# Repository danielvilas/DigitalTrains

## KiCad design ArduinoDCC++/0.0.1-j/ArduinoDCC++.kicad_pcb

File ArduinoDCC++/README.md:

# Arduino DCC++ Board
This board is designed to have the arduino core and the motor shield on one single board. 
One objective is to study the pinout change of the motor shield for DCC++

## Status
Deprecated, The new Dcc++EX project have an updated pinout that solves the need of this board. Also, for the shake of the price, this board has been separated on several independent boards, under [DccBlock](../DccBlocks) project.

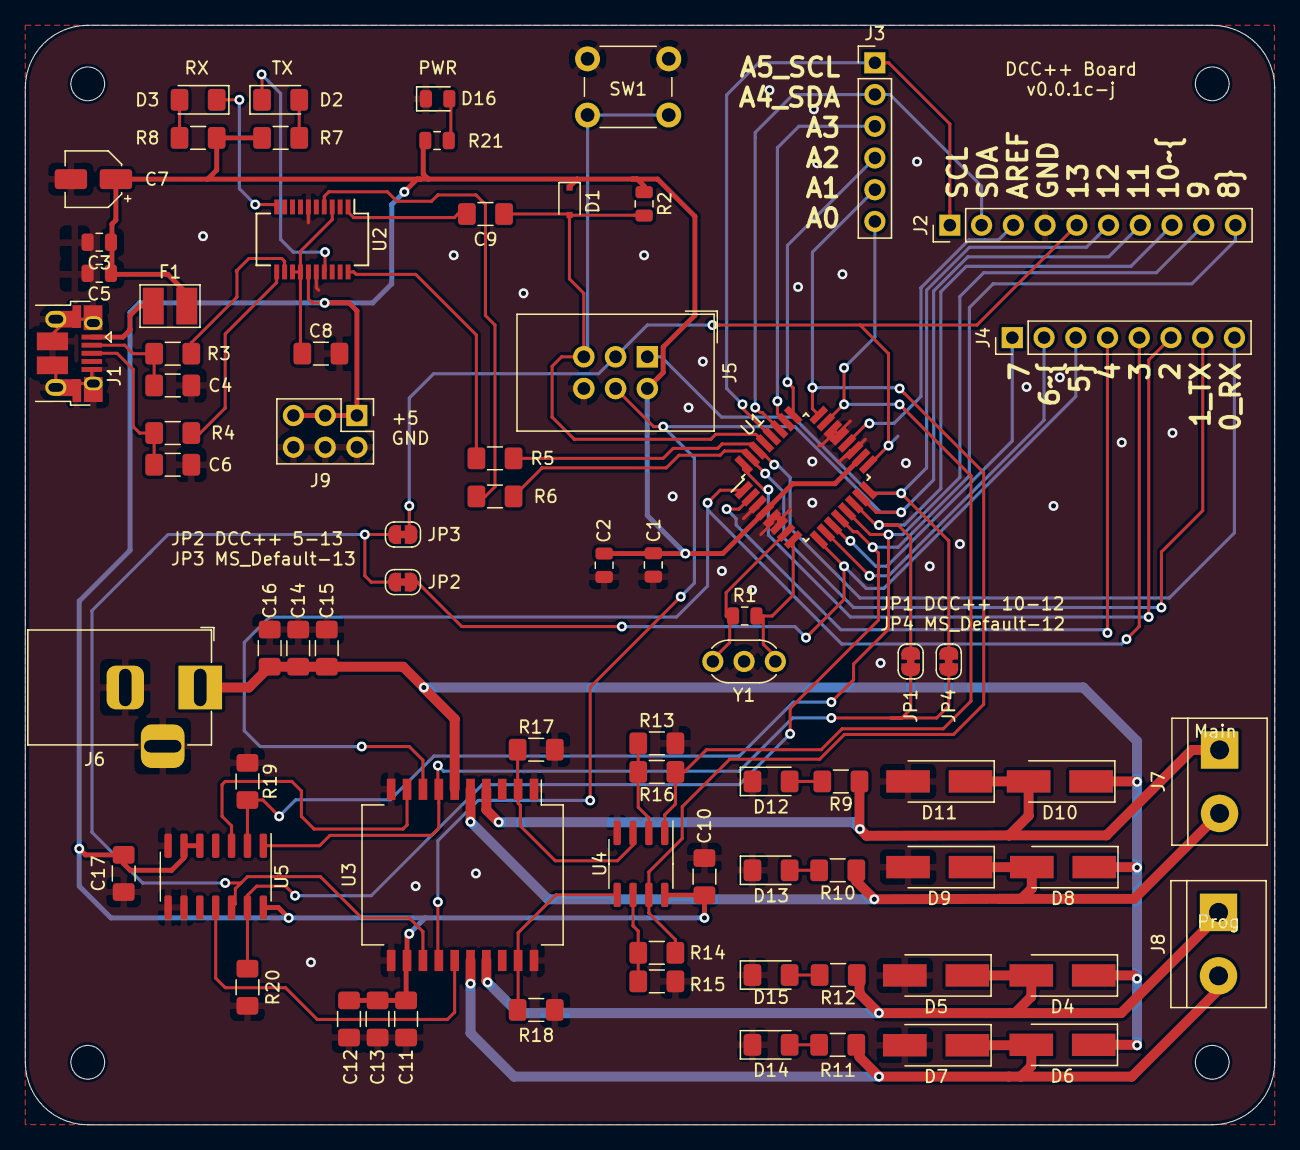
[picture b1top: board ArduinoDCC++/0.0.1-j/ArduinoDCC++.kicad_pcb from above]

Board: 2 copper layers, 100.0 x 88.0 mm, 79 parts (0 on the bottom side), 57 nets.

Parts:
C1, C2, C5: 100nF; C_0805_2012Metric
C3: 10nF; C_0805_2012Metric
C4, C6: 47pF; C_1206_3216Metric_Pad1.42x1.75mm_HandSolder
C7: 4.7uf; CP_Elec_4x5.3
C8, C9, C10, C11, C13, C17: 100nF; C_1206_3216Metric_Pad1.42x1.75mm_HandSolder
C12, C14, C15, C16: 10uF 35V; C_1206_3216Metric_Pad1.42x1.75mm_HandSolder
D1: 1N4148WS; D_SOD-323F
D2: TX_LED_Y; LED_1206_3216Metric_Pad1.42x1.75mm_HandSolder
D3: RX_LED_Y; LED_1206_3216Metric_Pad1.42x1.75mm_HandSolder
D4, D5, D6, D7, D8, D9, D10, D11: ss14; D_SMA_Handsoldering
D12: MJ_LED_Y; LED_1206_3216Metric_Pad1.42x1.75mm_HandSolder
D13, D15: PK_LED_Y; LED_1206_3216Metric_Pad1.42x1.75mm_HandSolder
D14: PJ_LED_Y; LED_1206_3216Metric_Pad1.42x1.75mm_HandSolder
D16: PWR_G; LED_0805_2012Metric
F1: MF-MSMF050-2; MF-MSMF
H1, H2, H3, H4: MountingHole; MountingHole_2.7mm_M2.5
J1: USB_B_Micro; USB_Micro-B_Amphenol_10103594-0001LF_Horizontal
J2: Conn_01x10; PinHeader_1x10_P2.54mm_Vertical
J3: Conn_01x06; PinHeader_1x06_P2.54mm_Vertical
J4: Conn_01x08; PinHeader_1x08_P2.54mm_Vertical
J5: ICSP; IDC-Header_2x03_P2.54mm_Vertical
J6: Barrel_Jack_Switch; BarrelJack_Horizontal
J7, J8: Screw_Terminal_01x02; TerminalBlock_bornier-2_P5.08mm
J9: Conn_02x03_Odd_Even; PinHeader_2x03_P2.54mm_Vertical
JP1, JP2, JP3, JP4: Jumper; SolderJumper-2_P1.3mm_Bridged_RoundedPad1.0x1.5mm
R1: 1M; R_0805_2012Metric
R2: 10K; R_0805_2012Metric
R3, R4: 27R; R_1206_3216Metric_Pad1.42x1.75mm_HandSolder
R5, R6, R7, R8, R13, R14: 1K; R_1206_3216Metric_Pad1.42x1.75mm_HandSolder
R9, R10, R11, R12, R15, R16, R19, R20: 10K; R_1206_3216Metric_Pad1.42x1.75mm_HandSolder
R17, R18: 0R15; R_1206_3216Metric_Pad1.42x1.75mm_HandSolder
R21: 1K; R_0805_2012Metric
SW1: SW_Push; SW_PUSH_6mm_H4.3mm
U1: ATmega328PB-AU; TQFP-32_7x7mm_P0.8mm
U2: FT231XS; SSOP-20_3.9x8.7mm_P0.635mm
U3: L298P; HSOP-20-1EP_11.0x15.9mm_P1.27mm_SlugUp
U4: LMV358; SOIC-8_3.9x4.9mm_P1.27mm
U5: 4077; SOIC-14_3.9x8.7mm_P1.27mm
Y1: CSTLS16M0X53-A0; Resonator_muRata_CSTLSxxxX-3Pin_W5.5mm_H3.0mm

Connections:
+5V: C1.2, C2.1, C3.1, C5.1, C7.1, C10.1, C11.1, C12.2, C13.2, C17.1, D1.1, F1.1, J5.2, J9.1, J9.3, J9.5, R2.1, R7.1, R8.1, R21.1, U1.4, U1.18, U2.15, U3.12, U4.8, U5.5, U5.6, U5.14
/Arduino/ad_2_int0: J4.6, U1.32
/Arduino/ap_3*_int1: J4.5, U1.1, U3.8
/Arduino/ap_4_t0: J4.4, U1.2
/Arduino/ap_5*_t1: J4.3, JP2.2, U1.9
/Arduino/ap_6*_ain0: J4.2, U1.10
/Arduino/ap_7_ain1: J4.1, U1.11
/Arduino/ap_8_icp: J2.10, R20.2, U1.12, U5.13
/Arduino/ap_9*_osc1: J2.9, R19.2, U1.13, U5.2
/Arduino/ap_10_ss: J2.8, JP1.2, U1.14
/Arduino/ap_11*_mosi: J2.7, J5.4, U1.15, U3.14
/Arduino/ap_12_miso: J2.6, J5.1, JP4.2, U1.16
/Arduino/ap_13_sck: J2.5, J5.3, JP3.1, U1.17
/Arduino/ap_a2: J3.4, U1.25
/Arduino/ap_a3: J3.3, U1.26
/Arduino/ap_a4_sda: J2.2, J3.2, U1.27
/Arduino/ap_a5_scl: J2.1, J3.1, U1.28
/Arduino/ap_aref: J2.3, U1.20
/FTDI 231/D+: C6.1, J1.3, R4.2
/FTDI 231/D-: C4.1, J1.2, R3.2
/FTDI 231/RST: C9.1, D1.2, J5.5, R2.2, SW1.2, U1.29
/FTDI 231/RX: J4.7, R6.1, U1.31
/FTDI 231/TX: J4.8, R5.1, U1.30
/Motor Shield/MainJ: D10.2, D11.1, J7.1, R9.1, U3.4
/Motor Shield/MainK: D8.2, D9.1, J7.2, R10.1, U3.5
/Motor Shield/ProgJ: D6.2, D7.1, J8.2, R11.1, U3.16
/Motor Shield/ProgK: D4.2, D5.1, J8.1, R12.1, U3.17
/Motor Shield/SNS0_aA0: J3.6, R16.1, U1.23, U4.1
/Motor Shield/SNS1_aA1: J3.5, R15.1, U1.24, U4.7
/Motor Shield/VMot: C14.2, C15.2, C16.2, D4.1, D6.1, D8.1, D10.1, J6.1, U3.6
/Motor Shield/dirA#: U3.9, U5.3
/Motor Shield/dirB#: U3.15, U5.11
/Motor Shield/dirB_a13: JP2.1, JP3.2, U3.13, U5.12
/Motor Shield/diraA_a12: JP1.1, JP4.1, U3.7, U5.1
/Motor Shield/snsA: R17.1, U3.2, U4.3
/Motor Shield/snsB: R18.1, U3.19, U4.5
GND: C1.1, C2.2, C3.2, C4.2, C5.2, C6.2, C7.2, C8.2, C10.2, C11.2, C12.1, C13.1, C14.1, C15.1, C16.1, C17.2, D5.2, D7.2, D9.2, D11.2, D12.1, D13.1, D14.1, D15.1, D16.1, J1.5, J1.6, J2.4, J5.6, J6.2, J6.3, J9.2, J9.4, J9.6, R13.2, R14.2, R17.2, R18.2, R19.1, R20.1, SW1.1, U1.3, U1.5, U1.6, U1.19, U1.21, U1.22, U2.6, U2.16, U3.1, U3.10, U3.11, U3.20, U4.4, U5.7, U5.8, U5.9, Y1.2
unnamed: C8.1, U2.3, U2.13, U2.14
unnamed: C9.2, U2.1
unnamed: D2.1, U2.17
unnamed: D2.2, R7.2
unnamed: D3.1, U2.10
unnamed: D3.2, R8.2
unnamed: D12.2, R9.2
unnamed: D13.2, R10.2
unnamed: D14.2, R11.2
unnamed: D15.2, R12.2
unnamed: D16.2, R21.2
unnamed: F1.2, J1.1
unnamed: R1.1, U1.7, Y1.3
unnamed: R1.2, U1.8, Y1.1
unnamed: R3.1, U2.12
unnamed: R4.1, U2.11
unnamed: R5.2, U2.20
unnamed: R6.2, U2.4
unnamed: R13.1, R16.2, U4.2
unnamed: R14.1, R15.2, U4.6

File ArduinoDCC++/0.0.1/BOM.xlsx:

Reference | Quantity | Value | Footprint | Datasheet
U5 | 1 | 4077 | Package_SO:SOIC-14_3.9x8.7mm_P1.27mm | http://www.intersil.com/content/dam/Intersil/documents/cd40/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
R17 R18 | 2 | 0R15 | Resistor_SMD:R_1206_3216Metric_Pad1.42x1.75mm_HandSolder | ~
C2 C1 C5 C8 C9 C10 C17 C11 C13 | 9 | 100nF | Capacitor_SMD:C_1206_3216Metric_Pad1.42x1.75mm_HandSolder | ~
R2 R10 R9 R12 R11 R16 R15 R19 R20 | 9 | 10K | Resistor_SMD:R_1206_3216Metric_Pad1.42x1.75mm_HandSolder | ~
C3 | 1 | 10nF | Capacitor_SMD:C_1206_3216Metric_Pad1.42x1.75mm_HandSolder | ~
C12 C15 C14 C16 | 4 | 10uF 35V | Capacitor_SMD:C_1206_3216Metric_Pad1.42x1.75mm_HandSolder | ~
R21 R8 R7 R5 R6 R13 R14 | 7 | 1K | Resistor_SMD:R_1206_3216Metric_Pad1.42x1.75mm_HandSolder | ~
R1 | 1 | 1M | Resistor_SMD:R_1206_3216Metric_Pad1.42x1.75mm_HandSolder | ~
R3 R4 | 2 | 27R | Resistor_SMD:R_1206_3216Metric_Pad1.42x1.75mm_HandSolder | ~
C7 | 1 | 4.7uf | Capacitor_SMD:CP_Elec_4x5.3 | ~
C4 C6 | 2 | 47pF | Capacitor_SMD:C_1206_3216Metric_Pad1.42x1.75mm_HandSolder | ~
U1 | 1 | ATmega328PB-AU | Package_QFP:TQFP-32_7x7mm_P0.8mm | http://ww1.microchip.com/downloads/en/DeviceDoc/40001906C.pdf
Y1 | 1 | AWSCR-16.00MTD-T | ArduinoDCC++:Resonator-AWSCR-16.00MTD-T | ~
J6 | 1 | Barrel_Jack_Switch | Connector_BarrelJack:BarrelJack_Horizontal | ~
D1 | 1 | CD1206-S01575 | Diode_SMD:D_1206_3216Metric_Pad1.42x1.75mm_HandSolder | ~
J3 | 1 | Conn_01x06 | Connector_PinHeader_2.54mm:PinHeader_1x06_P2.54mm_Vertical | ~
J4 | 1 | Conn_01x08 | Connector_PinHeader_2.54mm:PinHeader_1x08_P2.54mm_Vertical | ~
J2 | 1 | Conn_01x10 | Connector_PinHeader_2.54mm:PinHeader_1x10_P2.54mm_Vertical | ~
U2 | 1 | FT231XS | Package_SO:SSOP-20_3.9x8.7mm_P0.635mm | https://www.ftdichip.com/Support/Documents/DataSheets/ICs/DS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
J5 | 1 | ICSP | Connector_IDC:IDC-Header_2x03_P2.54mm_Vertical | ~
JP2 JP1 | 2 | Jumper | Jumper:SolderJumper-2_P1.3mm_Bridged_RoundedPad1.0x1.5mm | ~
U3 | 1 | L298P | Package_SO:HSOP-20-1EP_11.0x15.9mm_P1.27mm_SlugUp | http://www.st.com/st-web-ui/static/active/en/resource/techni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
U4 | 1 | LMV358 | Package_SO:SOIC-8_3.9x4.9mm_P1.27mm | http://www.ti.com/lit/ds/symlink/lmv324.pdf
F1 | 1 | MF-MSMF050-2 | Resistor_SMD:R_1206_3216Metric_Pad1.42x1.75mm_HandSolder | ~
D12 | 1 | MJ_LED_Y | LED_SMD:LED_1206_3216Metric_Pad1.42x1.75mm_HandSolder | ~
D14 | 1 | PJ_LED_Y | LED_SMD:LED_1206_3216Metric_Pad1.42x1.75mm_HandSolder | ~
D13 D15 | 2 | PK_LED_Y | LED_SMD:LED_1206_3216Metric_Pad1.42x1.75mm_HandSolder | ~
D3 | 1 | RX_LED_Y | LED_SMD:LED_1206_3216Metric_Pad1.42x1.75mm_HandSolder | ~
D16 | 1 | RX_PWR_G | LED_SMD:LED_1206_3216Metric_Pad1.42x1.75mm_HandSolder | ~
J7 J8 | 2 | Screw_Terminal_01x02 | TerminalBlock:TerminalBlock_bornier-2_P5.08mm | ~
D5 D7 D9 D11 D10 D8 D6 D4 | 8 | ss14 | Diode_SMD:D_SMA_Handsoldering | ~
SW1 | 1 | SW_Push | Button_Switch_THT:SW_PUSH_6mm_H4.3mm | ~
D2 | 1 | TX_LED_Y | LED_SMD:LED_1206_3216Metric_Pad1.42x1.75mm_HandSolder | ~
J1 | 1 | USB_B_Micro | Connector_USB:USB_Micro-B_Amphenol_10103594-0001LF_Horizontal | ~
 | 72
 | Farnell | 121,32 €

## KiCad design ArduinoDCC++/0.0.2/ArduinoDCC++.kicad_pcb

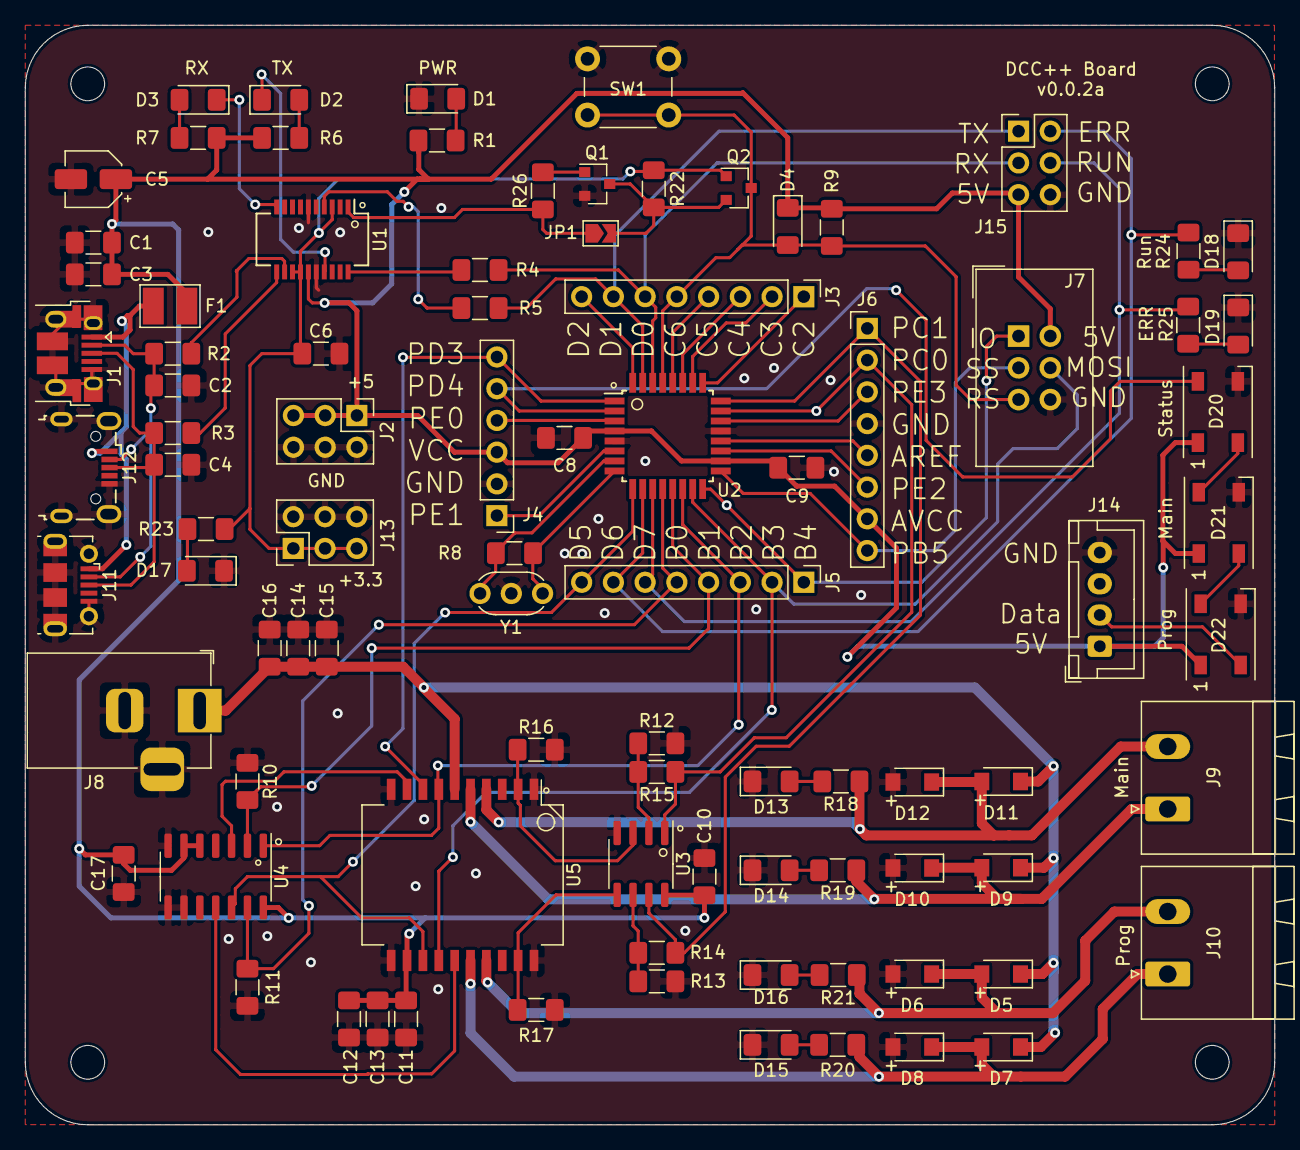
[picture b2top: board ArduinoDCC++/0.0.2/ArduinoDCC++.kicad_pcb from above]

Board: 2 copper layers, 100.0 x 88.0 mm, 94 parts (0 on the bottom side), 67 nets.

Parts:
C1: 10nF; C_1206_3216Metric_Pad1.42x1.75mm_HandSolder
C2, C4: 47pF; C_1206_3216Metric_Pad1.42x1.75mm_HandSolder
C3, C6, C8, C9, C10, C11, C13, C17: 100nF; C_1206_3216Metric_Pad1.42x1.75mm_HandSolder
C5: 4.7uf; CP_Elec_4x5.3
C12, C14, C15, C16: 10uF 35V; C_1206_3216Metric_Pad1.42x1.75mm_HandSolder
D1, D18: LED_GREEN; LED_1206_3216Metric_Pad1.42x1.75mm_HandSolder
D2, D3, D13, D14, D15, D16, D17: LED_YELLOW; LED_1206_3216Metric_Pad1.42x1.75mm_HandSolder
D4: CD1206-S01575; D_1206_3216Metric_Pad1.42x1.75mm_HandSolder
D5, D6, D7, D8, D9, D10, D11, D12: ss14; D_Sub_SMA
D19: LED_RED; LED_1206_3216Metric_Pad1.42x1.75mm_HandSolder
D20, D21, D22: WS2812B; LED_WS2812B_PLCC4_5.0x5.0mm_P3.2mm
F1: MF-MSMF050-2; MF-MSMF
H1, H2, H3, H4: MountingHole; MountingHole_2.7mm_M2.5
J1: USB_B_Micro; USB_Micro-B_Amphenol_10103594-0001LF_Horizontal
J2, J13, J15: Conn_02x03_Odd_Even; PinHeader_2x03_P2.54mm_Vertical
J3, J5, J6: Conn_01x08; PinHeader_1x08_P2.54mm_Vertical
J4: Conn_01x06; PinHeader_1x06_P2.54mm_Vertical
J7: ICSP; IDC-Header_2x03_P2.54mm_Vertical
J8: Barrel_Jack_Switch; BarrelJack_Horizontal
J9, J10: Screw_Terminal_01x02; PhoenixContact_MSTBA_2,5_2-G_1x02_P5.00mm_Horizontal
J11: USB_B_Micro; USB_Micro-B_Molex-105017-0001
J12: USB_B_Micro; USB_Micro-B_Wuerth_629105150521
J14: Conn_01x04; JST_XH_B4B-XH-A_1x04_P2.50mm_Vertical
JP1: Jumper_NO_Small; SolderJumper-2_P1.3mm_Open_TrianglePad1.0x1.5mm
Q1: BC849; SOT-23
Q2: 2N7002; SOT-23
R1, R4, R5, R6, R7, R12, R13, R23, R24, R25: 1K; R_1206_3216Metric_Pad1.42x1.75mm_HandSolder
R2, R3: 27R; R_1206_3216Metric_Pad1.42x1.75mm_HandSolder
R8: 1M; R_1206_3216Metric_Pad1.42x1.75mm_HandSolder
R9, R10, R11, R14, R15, R18, R19, R20, R21, R22, R26: 10K; R_1206_3216Metric_Pad1.42x1.75mm_HandSolder
R16, R17: 0R15; R_1206_3216Metric_Pad1.42x1.75mm_HandSolder
SW1: SW_Push; SW_PUSH_6mm_H4.3mm
U1: FT231XS; SSOP-20_3.9x8.7mm_P0.635mm
U2: ATmega328PB-AU; TQFP-32_7x7mm_P0.8mm
U3: LMV358; SOIC-8_3.9x4.9mm_P1.27mm
U4: 4077; SOIC-14_3.9x8.7mm_P1.27mm
U5: L298P; HSOP-20-1EP_11.0x15.9mm_P1.27mm_SlugUp
Y1: CSTLS16M0X53-A0; Resonator_muRata_CSTLSxxxX-3Pin_W5.5mm_H3.0mm

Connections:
+3V3: C6.1, J13.1, J13.3, J13.5, Q2.1, R22.2, R23.1, U1.3, U1.13, U1.14
+5V: C1.1, C3.1, C5.1, C8.2, C9.1, C10.1, C11.1, C12.2, C13.2, C17.1, D4.1, D20.1, D21.1, D22.1, F1.1, J2.1, J2.3, J2.5, J4.3, J6.7, J7.2, J14.1, J15.5, R1.1, R6.1, R7.1, R9.1, U1.15, U2.4, U2.18, U3.8, U4.5, U4.6, U4.14, U5.12
/ARef: J6.5, U2.20
/FTDI 231/D+: C4.1, J1.3, J11.3, J12.3, R3.2
/FTDI 231/D-: C2.1, J1.2, J11.2, J12.2, R2.2
/FTDI 231/DTR: JP1.1, R26.1, U1.1
/Motor Shield/MainJ: D11.2, D12.1, J9.2, R18.1, U5.4
/Motor Shield/MainK: D9.2, D10.1, J9.1, R19.1, U5.5
/Motor Shield/ProgJ: D7.2, D8.1, J10.1, R20.1, U5.16
/Motor Shield/ProgK: D5.2, D6.1, J10.2, R21.1, U5.17
/Motor Shield/VMot: C14.2, C15.2, C16.2, D5.1, D7.1, D9.1, D11.1, J8.1, U5.6
/Motor Shield/dirA#: U4.3, U5.9
/Motor Shield/dirB#: U4.11, U5.15
/Motor Shield/snsA: R16.1, U3.3, U5.2
/Motor Shield/snsB: R17.1, U3.5, U5.19
/PB0: J5.5, R11.2, U2.12, U4.13
/PB1: J5.4, R10.2, U2.13, U4.2
/PB2: J5.3, U2.14, U4.1, U5.7
/PB3: J5.2, J7.4, U2.15, U5.14
/PB4: J5.1, J7.1, U2.16
/PB5: J6.8, J7.3, U2.17
/PC0: J6.2, R15.1, U2.23, U3.1
/PC1: J6.1, R14.1, U2.24, U3.7
/PC2: J3.1, U2.25
/PC3: J3.2, U2.26
/PC4: J3.3, U2.27
/PC5: J3.4, U2.28
/PC6: D4.2, J3.5, J7.5, Q2.3, R9.2, SW1.2, U2.29
/PD0: J3.6, J15.3, R4.1, U2.30
/PD1: J3.7, J15.1, R5.1, U2.31
/PD2: J3.8, U2.32
/PD3: J4.6, U2.1, U5.8
/PD4: D20.4, J4.5, U2.2
/PD5: J5.8, U2.9, U4.12, U5.13
/PD6: J5.7, J15.2, R24.1, U2.10
/PD7: J5.6, J15.4, R25.1, U2.11
/PE0: J4.4, U2.3
/PE1: J4.1, U2.6
/PE2: J6.6, U2.19
/PE3: J6.3, U2.22
GND: C1.2, C2.2, C3.2, C4.2, C5.2, C6.2, C8.1, C9.2, C10.2, C11.2, C12.1, C13.1, C14.1, C15.1, C16.1, C17.2, D1.1, D6.2, D8.2, D10.2, D12.2, D13.1, D14.1, D15.1, D16.1, D17.1, D18.1, D19.1, D20.3, D21.3, D22.3, J1.5, J1.6, J2.2, J2.4, J2.6, J4.2, J6.4, J7.6, J8.2, J8.3, J11.5, J11.6, J12.5, J12.6, J13.2, J13.4, J13.6, J14.4, J15.6, Q1.2, R10.1, R11.1, R12.2, R13.2, R16.2, R17.2, SW1.1, U1.6, U1.16, U2.5, U2.21, U3.4, U4.7, U4.8, U4.9, U5.1, U5.10, U5.11, U5.20, Y1.2
unnamed: D1.2, R1.2
unnamed: D2.1, U1.17
unnamed: D2.2, R6.2
unnamed: D3.1, U1.10
unnamed: D3.2, R7.2
unnamed: D13.2, R18.2
unnamed: D14.2, R19.2
unnamed: D15.2, R20.2
unnamed: D16.2, R21.2
unnamed: D17.2, R23.2
unnamed: D18.2, R24.2
unnamed: D19.2, R25.2
unnamed: D20.2, D21.4
unnamed: D21.2, D22.4
unnamed: D22.2, J14.2
unnamed: F1.2, J1.1, J11.1, J12.1
unnamed: JP1.2, Q1.3, Q2.2, R22.1
unnamed: Q1.1, R26.2
unnamed: R2.1, U1.12
unnamed: R3.1, U1.11
unnamed: R4.2, U1.20
unnamed: R5.2, U1.4
unnamed: R8.1, U2.7, Y1.3
unnamed: R8.2, U2.8, Y1.1
unnamed: R12.1, R15.2, U3.2
unnamed: R13.1, R14.2, U3.6

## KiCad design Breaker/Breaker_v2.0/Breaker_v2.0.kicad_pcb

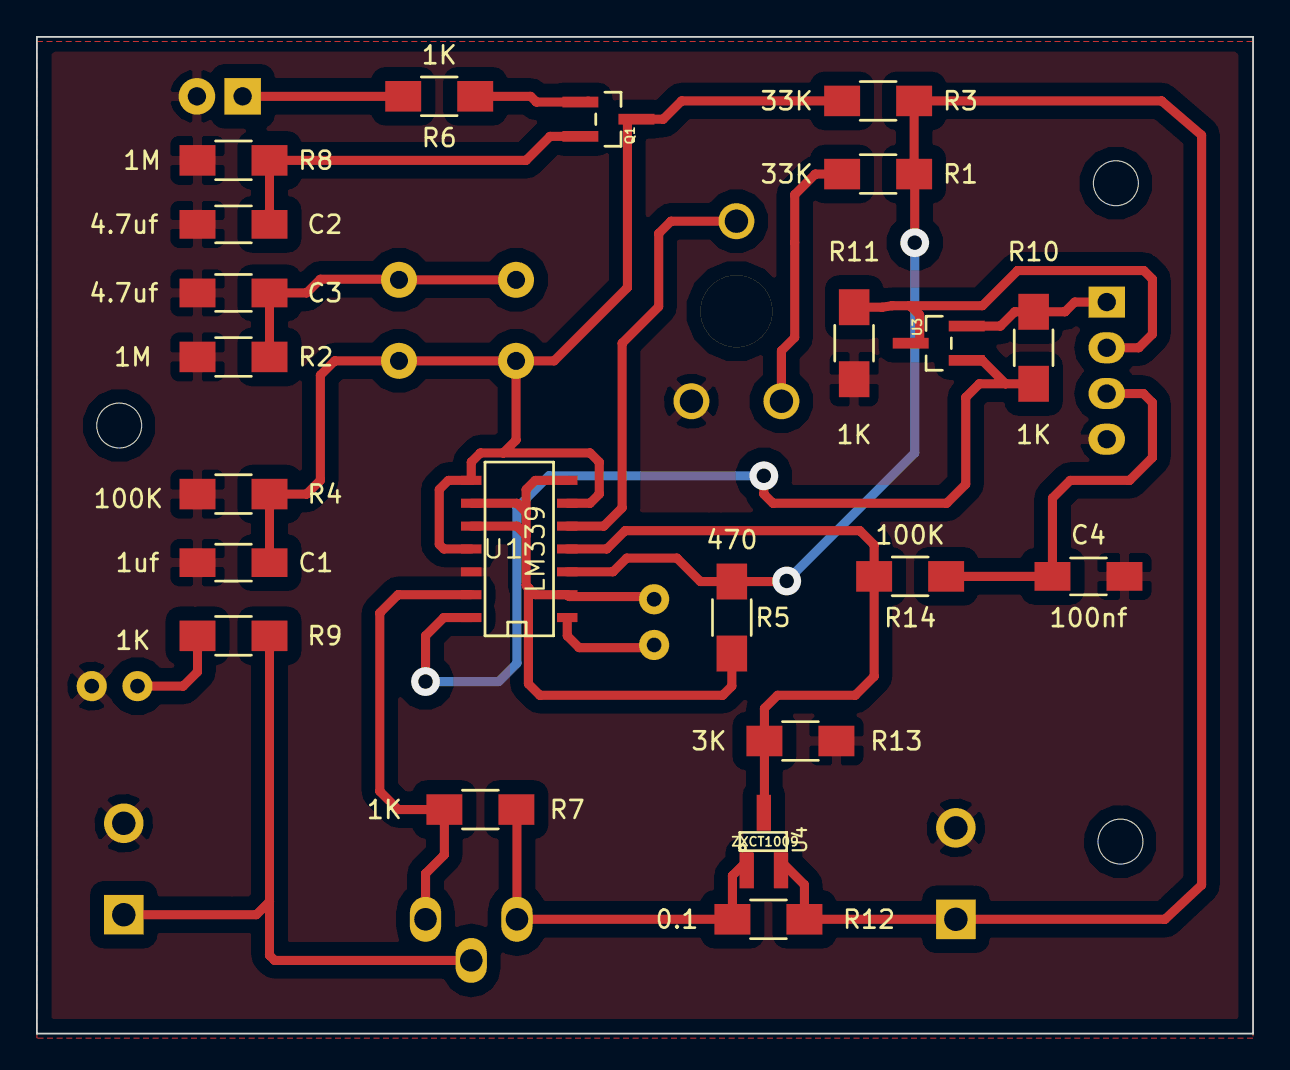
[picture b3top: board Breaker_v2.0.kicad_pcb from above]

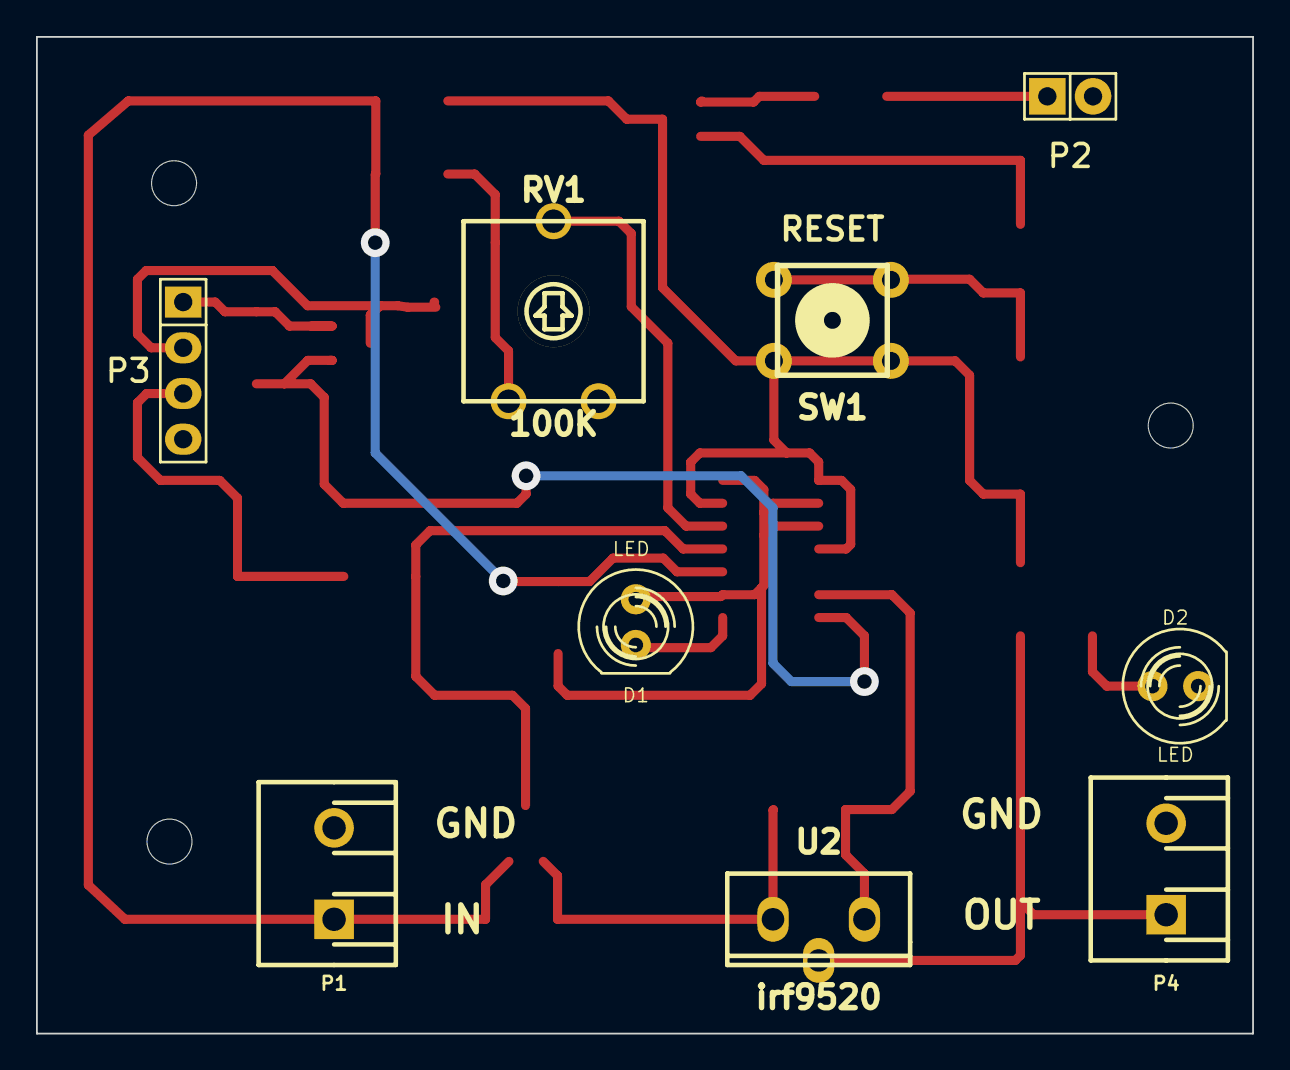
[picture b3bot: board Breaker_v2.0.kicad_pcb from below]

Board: 2 copper layers, 67.6 x 55.4 mm, 34 parts (9 on the bottom side), 20 nets.

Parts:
C1: 1uf; C_1206_HandSoldering
C2, C3: 4.7uf; C_1206_HandSoldering
C4: 100nf; C_1206_HandSoldering
D1, D2: LED; LED-5MM
MH: MountingHole_2-5mm_RevA_Date21Jun2010; MountingHole_2-5mm
MH#2, MH#3: MountingHole_2-5mm_RevA_Date21Jun2010; MountingHole_2-5mm
P1, P4: CONN_01X02; 1x2-SCREW-TERM_P200mil
P2: CONN_01X02; Pin_Header_Straight_1x02
P3: CONN_01X04; Pin_Header_Straight_1x04
Q1: QBC849B; sot23
R1, R3: 33K; R_1206_HandSoldering
R2, R8: 1M; R_1206_HandSoldering
R4, R14: 100K; R_1206_HandSoldering
R5: 470; R_1206_HandSoldering
R6, R7, R9, R10, R11: 1K; R_1206_HandSoldering
R12: 0.1; R_1206_HandSoldering
R13: 3K; R_1206_HandSoldering
RV1: 100K; trimmer_ecp_ca9-v10
SW1: RESET; PCB_PUSH
U1: LM339; SOIC-14_W
U2: irf9520; to220_std
U3: BSS84P; sot23
U4: ZXCT1009; SOT-23

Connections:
/LN: D1.1, R5.2, U1.2, U1.7, U1.9, U1.10
/LP: C1.1, Q1.3, R3.2, R4.1, SW1.1, SW1.3, U1.6, U1.8, U1.11
/RSN: R7.1, R12.1, U2.1, U4.1
/VO: R13.1, R14.2, U1.4, U4.3
/VREF: RV1.2, U1.5
CRST: P2.1, R6.2
ERR: P3.2, R11.1, U3.3
GND: C1.2, C2.2, C3.2, C4.2, D2.2, P1.2, P2.2, P3.4, P4.2, R2.2, R4.2, R8.2, R11.2, R13.2, RV1.3, U1.12
unnamed: C2.1, Q1.2, R8.1
unnamed: C3.1, R2.1, SW1.2, SW1.4
unnamed: D1.2, U1.1
unnamed: D2.1, R9.2
unnamed: Q1.1, R6.1
unnamed: R1.2, RV1.1
unnamed: R7.2, U1.13, U2.3
unnamed: R10.2, U1.14, U3.1
V5: P3.1, R10.1, U3.2
VCC: P1.1, R1.1, R3.1, R5.1, R12.2, U1.3, U4.2
VCC_P: P4.1, R9.1, U2.2
VF: C4.1, P3.3, R14.1

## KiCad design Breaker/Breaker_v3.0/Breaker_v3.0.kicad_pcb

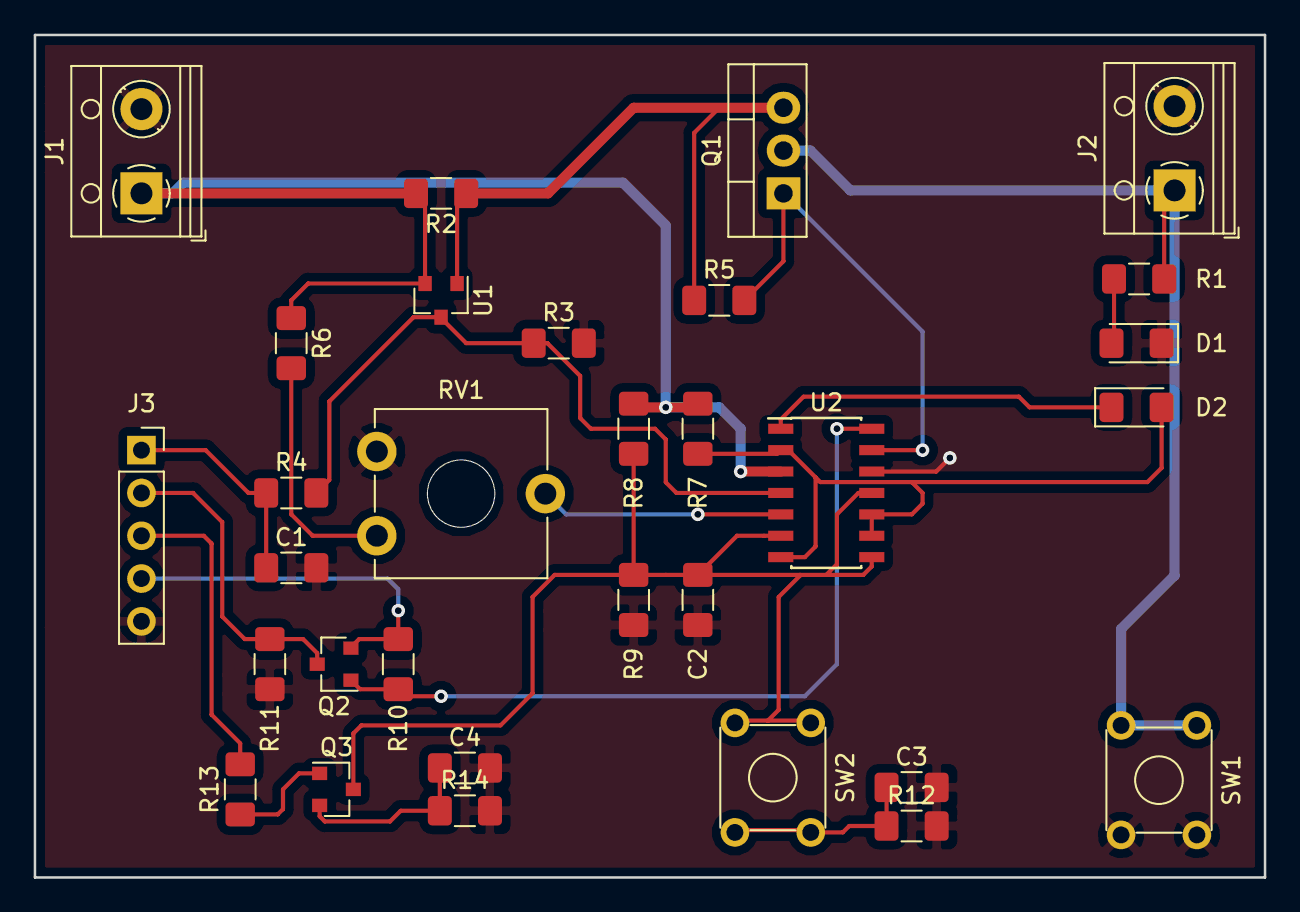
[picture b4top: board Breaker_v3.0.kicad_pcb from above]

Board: 2 copper layers, 73.0 x 50.0 mm, 31 parts (0 on the bottom side), 20 nets.

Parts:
C1: 100nf; C_1206_3216Metric_Pad1.42x1.75mm_HandSolder
C2: 1nf; C_1206_3216Metric_Pad1.42x1.75mm_HandSolder
C3, C4: 4.7uf; C_1206_3216Metric_Pad1.42x1.75mm_HandSolder
D1: Green; LED_1206_3216Metric_Pad1.42x1.75mm_HandSolder
D2: Red; LED_1206_3216Metric_Pad1.42x1.75mm_HandSolder
J1, J2: Screw_Terminal_01x02; TerminalBlock_RND_205-00012_1x02_P5.00mm_Horizontal
J3: Conn_01x05; PinSocket_1x05_P2.54mm_Vertical
Q1: IRF9520PBF; TO-220-3_Vertical
Q2: BSS84; SOT-23
Q3: BC849; SOT-23
R1: 1K; C_1206_3216Metric_Pad1.42x1.75mm_HandSolder
R2: 0.1; C_1206_3216Metric_Pad1.42x1.75mm_HandSolder
R3: 3K; R_1206_3216Metric_Pad1.42x1.75mm_HandSolder
R4, R9: 100K; R_1206_3216Metric_Pad1.42x1.75mm_HandSolder
R5, R10, R11, R13: 1K; R_1206_3216Metric_Pad1.42x1.75mm_HandSolder
R6, R8: 33K; R_1206_3216Metric_Pad1.42x1.75mm_HandSolder
R7: 470; R_1206_3216Metric_Pad1.42x1.75mm_HandSolder
R12, R14: 1M; R_1206_3216Metric_Pad1.42x1.75mm_HandSolder
RV1: 100K; Potentiometer_ACP_CA9-V10_Vertical_Hole
SW1: test; SW_TH_Tactile_Omron_B3F-10xx
SW2: SW_Push_Dual; SW_TH_Tactile_Omron_B3F-10xx
U1: ZXCT1009F; SOT-23
U2: LM339; SOIC-14_3.9x8.7mm_P1.27mm

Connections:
/Control Module/Vsense: R3.1, R4.2, U1.3, U2.4
/Control Module/ctrl_ref: C2.1, Q3.3, R8.2, R9.1, SW2.1, SW2.3, U2.6, U2.8, U2.11
/Control Module/cut_ref: RV1.2, U2.5
/Control Module/status: D2.2, R7.2, U2.2, U2.7, U2.9, U2.10
/Power Control/Vin: Q1.3, R2.1, R5.1, U1.1
/Power Control/Vout: J2.1, Q1.2, R1.1, SW1.1, SW1.3
/Vmean: C1.1, J3.1, R4.1
/ext_err: J3.2, Q2.3, R11.1
/ext_reset: J3.3, R13.2
/ext_v5: J3.4, Q2.2, R10.1
GND: C1.2, C2.2, C3.2, C4.2, D1.1, J1.2, J2.2, J3.5, R3.2, R9.2, R11.2, R12.2, R14.2, RV1.3, SW1.2, SW1.4, U2.12
unnamed: C3.1, R12.1, SW2.2, SW2.4
unnamed: C4.1, Q3.2, R14.1
unnamed: D1.2, R1.2
unnamed: D2.1, U2.1
unnamed: Q1.1, R5.2, U2.13
unnamed: Q2.1, R10.2, U2.14
unnamed: Q3.1, R13.1
unnamed: R6.2, RV1.1
VCC: J1.1, R2.2, R6.1, R7.1, R8.1, U1.2, U2.3

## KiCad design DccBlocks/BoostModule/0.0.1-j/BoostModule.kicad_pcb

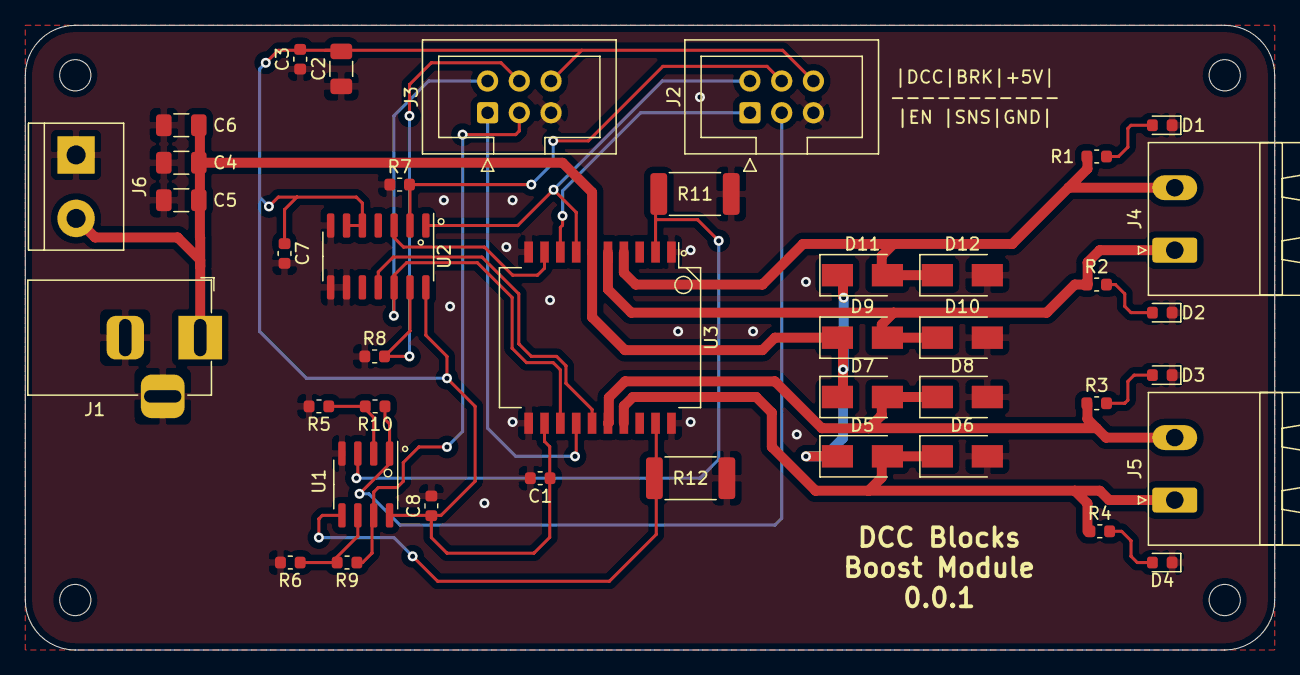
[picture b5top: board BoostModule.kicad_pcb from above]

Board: 2 copper layers, 100.0 x 50.0 mm, 45 parts (0 on the bottom side), 25 nets.

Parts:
C1, C3, C7, C8: 100nF; C_0603_1608Metric
C2, C4, C5, C6: 10uF 35V; C_1206_3216Metric
D1, D2, D3, D4: LED_YELLOW; LED_0603_1608Metric
D5, D6, D7, D8, D9, D10, D11, D12: ss14; D_SMA
H1, H2, H3, H4: MountingHole; MountingHole_2.5mm
J1: Barrel_Jack_Switch; BarrelJack_Horizontal
J2, J3: Conn_02x03_Odd_Even; IDC-Header_2x03_P2.54mm_Vertical
J4, J5: Screw_Terminal_01x02; PhoenixContact_MSTBA_2,5_2-G_1x02_P5.00mm_Horizontal
J6: Screw_Terminal_01x02; TerminalBlock_bornier-2_P5.08mm
R1, R2, R3, R4, R7, R8, R9, R10: 10K; R_0603_1608Metric
R5, R6: 1K; R_0603_1608Metric
R11, R12: 0R15; R_2512_6332Metric
U1: LMV358; SOIC-8_3.9x4.9mm_P1.27mm
U2: 4077; SOIC-14_3.9x8.7mm_P1.27mm
U3: L298P; HSOP-20-1EP_11.0x15.9mm_P1.27mm_SlugUp

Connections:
+5V: C1.1, C2.2, C3.2, C7.1, C8.1, J2.6, J3.6, U1.8, U2.5, U2.6, U2.14, U3.12
/BoosModule/Brake_A: J2.4, R7.2, U2.2
/BoosModule/Brake_B: J3.4, R8.2, U2.13
/BoosModule/DCC_A: J2.2, U2.1, U3.7
/BoosModule/DCC_B: J3.2, U2.12, U3.13
/BoosModule/Out_A_J: D11.2, D12.1, J4.2, R1.1, U3.4
/BoosModule/Out_A_K: D9.2, D10.1, J4.1, R2.1, U3.5
/BoosModule/Out_B_J: D7.2, D8.1, J5.2, R3.1, U3.16
/BoosModule/Out_B_K: D5.2, D6.1, J5.1, R4.1, U3.17
/BoosModule/Sns_A: J2.3, R10.1, U1.1
/BoosModule/Sns_B: J3.3, R9.1, U1.7
/BoosModule/dirA#: U2.3, U3.9
/BoosModule/dirB#: U2.11, U3.15
/BoosModule/en_A: J2.1, U3.8
/BoosModule/en_B: J3.1, U3.14
/BoosModule/snsA: R11.1, U1.3, U3.2
/BoosModule/snsB: R12.1, U1.5, U3.19
/V_DCC: C4.2, C5.2, C6.2, D5.1, D7.1, D9.1, D11.1, J1.1, J6.2, U3.6
GND: C1.2, C2.1, C3.1, C4.1, C5.1, C6.1, C7.2, C8.2, D1.1, D2.1, D3.1, D4.1, D6.2, D8.2, D10.2, D12.2, J1.2, J1.3, J2.5, J3.5, J6.1, R5.2, R6.2, R7.1, R8.1, R11.2, R12.2, U1.4, U2.7, U2.8, U2.9, U3.1, U3.10, U3.11, U3.20
unnamed: D1.2, R1.2
unnamed: D2.2, R2.2
unnamed: D3.2, R3.2
unnamed: D4.2, R4.2
unnamed: R6.1, R9.2, U1.6
unnamed: R5.1, R10.2, U1.2
